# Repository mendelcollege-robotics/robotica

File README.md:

# About
This is the repository for all the files associated with, and used to create, a soccer robot for participation in the [Robocup](https://www.robocup.org/leagues/18). Made by students of the Mendelcollege, from team 'Mendel'.

# Info:

  [Mendelcollege.nl](https://mendelcollege.nl/ontdek-je-talenten/robotica-en-beta/)

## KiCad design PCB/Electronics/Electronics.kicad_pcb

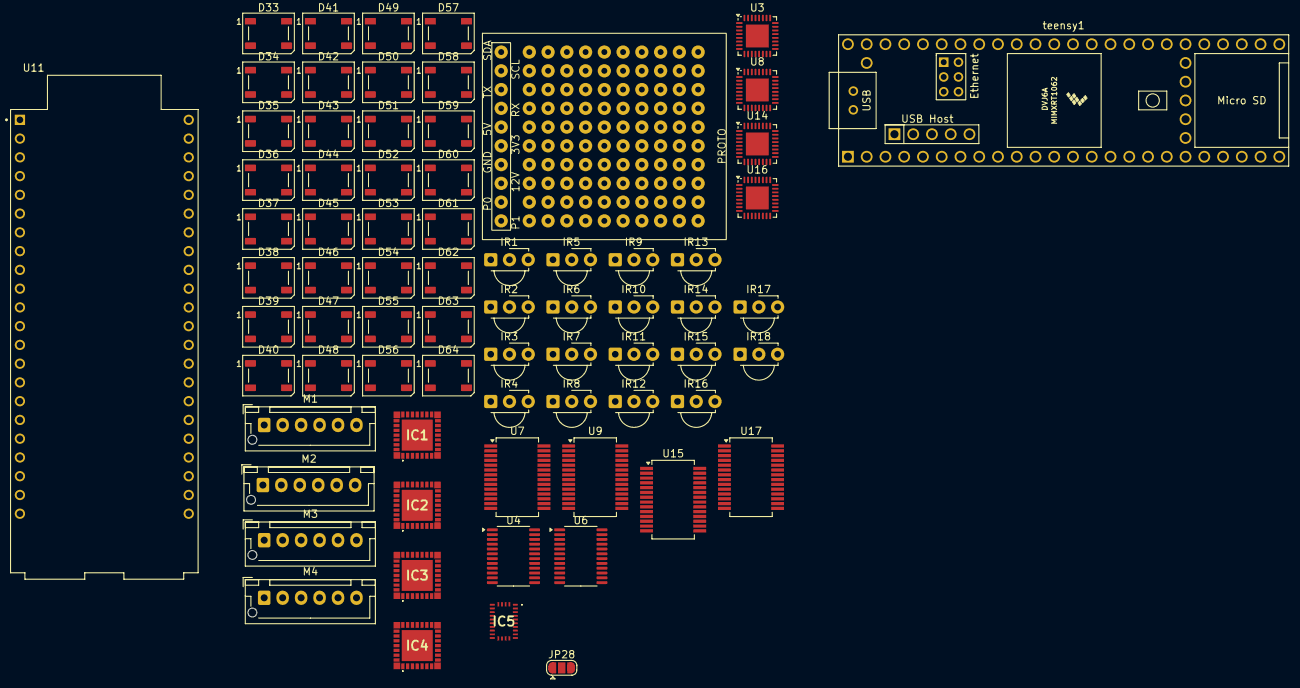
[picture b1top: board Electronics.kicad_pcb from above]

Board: 2 copper layers, 73 parts (0 on the bottom side), 102 nets, no tracks yet.

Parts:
D33, D34, D35, D36, D37, D38, D39, D40, D41, D42, D43, D44, D45, D46, D47, D48, D49, D50, D51, D52, D53, D54, D55, D56, D57, D58, D59, D60, D61, D62, D63, D64: WS2812B; LED_WS2812B_PLCC4_5.0x5.0mm_P3.2mm
IC1, IC2, IC3, IC4: TB9051FTG
IC5: BNO086
IR1, IR2, IR3, IR4, IR5, IR6, IR7, IR8, IR9, IR10, IR11, IR12, IR13, IR14, IR15, IR16, IR17, IR18: TSSP4038; Vishay_MINICAST-3Pin
JP28: SolderJumper_3_Bridged12; SolderJumper-3_P1.3mm_Open_RoundedPad1.0x1.5mm
M1, M2, M3, M4: JST_XH_B6B-XH-AM_1x06_P2.50mm_Vertical
U2: protoboard
U3, U8, U14, U16: ATmega328P-M; QFN-32-1EP_5x5mm_P0.5mm_EP3.1x3.1mm
U4, U6: TCA9548APWR; TSSOP-24_4.4x7.8mm_P0.65mm
U7, U9, U15, U17: FT232RL; SSOP-28_5.3x10.2mm_P0.65mm
U11: ESP32-S3-DEVKITM-1-N8; MODULE_ESP32-S3-DEVKITM-1-N8
teensy1: Teensy4.1; Teensy41

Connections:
+3.3V: U4.24 (VCC), U6.24 (VCC)
+3V3: IC5.3 (VDD), IC5.28 (VDDIO), U2.6 (3.3v), U11.J1_1 (3V3)
+5V: IC1.2 (VCC), IC2.2 (VCC), IC3.2 (VCC), IC4.2 (VCC), M1.3 (5V), M2.3 (5V), M3.3 (5V), M4.3 (5V), U2.5 (5v), U3.4 (VCC), U3.6 (VCC), U3.18 (AVCC), U7.4 (VCCIO), U7.20 (VCC), U8.4 (VCC), U8.6 (VCC), U8.18 (AVCC), U9.4 (VCCIO), U9.20 (VCC), U14.4 (VCC), U14.6 (VCC), U14.18 (AVCC), U15.4 (VCCIO), U15.20 (VCC), U16.4 (VCC), U16.6 (VCC), U16.18 (AVCC), U17.4 (VCCIO), U17.20 (VCC), teensy1.48 (VIN)
/5V: D33.1 (VDD), D34.1 (VDD), D35.1 (VDD), D36.1 (VDD), D37.1 (VDD), D38.1 (VDD), D39.1 (VDD), D40.1 (VDD), D41.1 (VDD), D42.1 (VDD), D43.1 (VDD), D44.1 (VDD), D45.1 (VDD), D46.1 (VDD), D47.1 (VDD), D48.1 (VDD), D49.1 (VDD), D50.1 (VDD), D51.1 (VDD), D52.1 (VDD), D53.1 (VDD), D54.1 (VDD), D55.1 (VDD), D56.1 (VDD), D57.1 (VDD), D58.1 (VDD), D59.1 (VDD), D60.1 (VDD), D61.1 (VDD), D62.1 (VDD), D63.1 (VDD), D64.1 (VDD)
/SCL: IC5.19 (H_SCL/SCK/RX), U2.1 (SCL), U4.22 (SCL), U6.22 (SCL), teensy1.41 (19_A5_SCL)
/SDA: IC5.20 (H_SDA/H_MISO/TX), U4.23 (SDA), U6.23 (SDA), teensy1.40 (18_A4_SDA)
/csn-imu: IC5.18 (H_CSN), teensy1.32 (40_A16)
/encA-m1: M4.5 (encA), U8.24 (PC1)
/encA-m2: M1.5 (encA), U3.24 (PC1)
/encA-m3: M2.5 (encA), U14.24 (PC1)
/encA-m4: M3.5 (encA), U16.24 (PC1)
/encB-m1: M4.6 (encB), U8.25 (PC2)
/encB-m2: M1.6 (encB), U3.25 (PC2)
/encB-m3: M2.6 (encB), U14.25 (PC2)
/encB-m4: M3.6 (encB), U16.25 (PC2)
/esp-rx: U11.J3_6 (U0TXD), teensy1.17 (25_A11_RX6_SDA2)
/esp-tx: U11.J3_5 (U0RXD), teensy1.16 (24_A10_TX6_SCL2)
/int-imu: IC5.14 (H_INTN), teensy1.31 (39_MISO1_OUT1A)
/out1-m1: IC1.13 (OUT1_1), IC1.14 (OUT1_2), M4.1 (+)
/out1-m2: IC2.13 (OUT1_1), IC2.14 (OUT1_2), M1.1 (+)
/out1-m3: IC3.13 (OUT1_1), IC3.14 (OUT1_2), M2.1 (+)
/out1-m4: IC4.13 (OUT1_1), IC4.14 (OUT1_2), M3.1 (+)
/out2-m1: IC1.22 (OUT2_1), IC1.23 (OUT2_2), M4.2 (-)
/out2-m2: IC2.22 (OUT2_1), IC2.23 (OUT2_2), M1.2 (-)
/out2-m3: IC3.22 (OUT2_1), IC3.23 (OUT2_2), M2.2 (-)
/out2-m4: IC4.22 (OUT2_1), IC4.23 (OUT2_2), M3.2 (-)
/pwm1-m1: IC1.8 (PWM1), U8.9 (PD5)
/pwm1-m2: IC2.8 (PWM1), U3.9 (PD5)
/pwm1-m3: IC3.8 (PWM1), U14.9 (PD5)
/pwm1-m4: IC4.8 (PWM1), U16.9 (PD5)
/pwm2-m1: IC1.9 (PWM2), U8.10 (PD6)
/pwm2-m2: IC2.9 (PWM2), U3.10 (PD6)
/pwm2-m3: IC3.9 (PWM2), U14.10 (PD6)
/pwm2-m4: IC4.9 (PWM2), U16.10 (PD6)
/rst-imu: IC5.11 (NRST), teensy1.33 (41_A17)
/rx-m1: U9.1 (TXD), teensy1.2 (0_RX1_CRX2_CS1)
/rx-m2: U7.1 (TXD), teensy1.9 (7_RX2_OUT1A)
/rx-m3: U15.1 (TXD), teensy1.20 (28_RX7)
/rx-m4: U17.1 (TXD), teensy1.26 (34_RX8)
/rx-proto: U2.4 (RX), teensy1.37 (15_A1_RX3_SPDIF_IN)
/tx-m1: U9.5 (RXD), teensy1.3 (1_TX1_CTX2_MISO1)
/tx-m2: U7.5 (RXD), teensy1.10 (8_TX2_IN1)
/tx-m3: U15.5 (RXD), teensy1.21 (29_TX7)
/tx-m4: U17.5 (RXD), teensy1.27 (35_TX8)
/tx-proto: U2.3 (TX), teensy1.36 (14_A0_TX3_SPDIF_OUT)
/vout-m1: IC1.11 (VBAT_1), IC1.12 (VBAT_2), IC1.24 (VBAT_3), IC1.25 (VBAT_4)
/vout-m2: IC2.11 (VBAT_1), IC2.12 (VBAT_2), IC2.24 (VBAT_3), IC2.25 (VBAT_4)
/vout-m3: IC3.11 (VBAT_1), IC3.12 (VBAT_2), IC3.24 (VBAT_3), IC3.25 (VBAT_4)
/vout-m4: IC4.11 (VBAT_1), IC4.12 (VBAT_2), IC4.24 (VBAT_3), IC4.25 (VBAT_4)
GND: D33.3 (VSS), D34.3 (VSS), D35.3 (VSS), D36.3 (VSS), D37.3 (VSS), D38.3 (VSS), D39.3 (VSS), D40.3 (VSS), D41.3 (VSS), D42.3 (VSS), D43.3 (VSS), D44.3 (VSS), D45.3 (VSS), D46.3 (VSS), D47.3 (VSS), D48.3 (VSS), D49.3 (VSS), D50.3 (VSS), D51.3 (VSS), D52.3 (VSS), D53.3 (VSS), D54.3 (VSS), D55.3 (VSS), D56.3 (VSS), D57.3 (VSS), D58.3 (VSS), D60.3 (VSS), D61.3 (VSS), D62.3 (VSS), D63.3 (VSS), D64.3 (VSS), IC1.4 (AGND), IC1.15 (PGND_1), IC1.16 (PGND_2), IC1.17 (PGND_3), IC1.19 (PGND_4), IC1.20 (PGND_5), IC1.21 (PGND_6), IC1.27 (TEST1), IC1.28 (TEST2), IC1.29 (EP), IC1.C1 (CORNER1), IC1.C2 (CORNER2), IC1.C3 (CORNER3), IC1.C4 (CORNER4), IC2.4 (AGND), IC2.15 (PGND_1), IC2.16 (PGND_2), IC2.17 (PGND_3), IC2.19 (PGND_4), IC2.20 (PGND_5), IC2.21 (PGND_6), IC2.27 (TEST1), IC2.28 (TEST2), IC2.29 (EP), IC2.C1 (CORNER1), IC2.C2 (CORNER2), IC2.C3 (CORNER3), IC2.C4 (CORNER4), IC3.4 (AGND), IC3.15 (PGND_1), IC3.16 (PGND_2), IC3.17 (PGND_3), IC3.19 (PGND_4), IC3.20 (PGND_5), IC3.21 (PGND_6), IC3.27 (TEST1), IC3.28 (TEST2), IC3.29 (EP), IC3.C1 (CORNER1), IC3.C2 (CORNER2), IC3.C3 (CORNER3), IC3.C4 (CORNER4), IC4.4 (AGND), IC4.15 (PGND_1), IC4.16 (PGND_2), IC4.17 (PGND_3), IC4.19 (PGND_4), IC4.20 (PGND_5), IC4.21 (PGND_6), IC4.27 (TEST1), IC4.28 (TEST2), IC4.29 (EP), IC4.C1 (CORNER1), IC4.C2 (CORNER2), IC4.C3 (CORNER3), IC4.C4 (CORNER4), IC5.2 (GND_1), IC5.10 (CLKSEL0), IC5.25 (GND_2), IR1.2 (GND), IR2.2 (GND), IR3.2 (GND), IR4.2 (GND), IR5.2 (GND), IR6.2 (GND), IR7.2 (GND), IR8.2 (GND), IR9.2 (GND), IR10.2 (GND), IR11.2 (GND), IR12.2 (GND), IR13.2 (GND), IR14.2 (GND), IR15.2 (GND), IR16.2 (GND), IR17.2 (GND), IR18.2 (GND), M1.4 (GND), M2.4 (GND), M3.4 (GND), M4.4 (GND), U2.7 (gnd), U3.3 (GND), U3.5 (GND), U3.21 (GND), U3.33 (GND), U4.12 (GND), U6.12 (GND), U7.7 (GND), U7.18 (GND), U7.21 (GND), U7.25 (AGND), U7.26 (TEST), U8.3 (GND), U8.5 (GND), U8.21 (GND), U8.33 (GND), U9.7 (GND), U9.18 (GND), U9.21 (GND), U9.25 (AGND), U9.26 (TEST), U11.J3_1 (GND_J3_1), U14.3 (GND), U14.5 (GND), U14.21 (GND), U14.33 (GND), U15.7 (GND), U15.18 (GND), U15.21 (GND), U15.25 (AGND), U15.26 (TEST), U16.3 (GND), U16.5 (GND), U16.21 (GND), U16.33 (GND), U17.7 (GND), U17.18 (GND), U17.21 (GND), U17.25 (AGND), U17.26 (TEST), teensy1.1 (GND), teensy1.34 (GND), teensy1.47 (GND)
unnamed: D33.2 (DOUT), D37.4 (DIN)
unnamed: D34.4 (DIN), D61.2 (DOUT)
unnamed: D34.2 (DOUT), D38.4 (DIN)
unnamed: D35.4 (DIN), D62.2 (DOUT)
unnamed: D35.2 (DOUT), D39.4 (DIN)
unnamed: D36.4 (DIN), D63.2 (DOUT)
unnamed: D36.2 (DOUT), D40.4 (DIN)
unnamed: D37.2 (DOUT), D41.4 (DIN)
unnamed: D38.2 (DOUT), D42.4 (DIN)
unnamed: D39.2 (DOUT), D43.4 (DIN)
unnamed: D40.2 (DOUT), D44.4 (DIN)
unnamed: D41.2 (DOUT), D45.4 (DIN)
unnamed: D42.2 (DOUT), D46.4 (DIN)
unnamed: D43.2 (DOUT), D47.4 (DIN)
unnamed: D44.2 (DOUT), D48.4 (DIN)
unnamed: D45.2 (DOUT), D49.4 (DIN)
unnamed: D46.2 (DOUT), D50.4 (DIN)
unnamed: D47.2 (DOUT), D51.4 (DIN)
unnamed: D48.2 (DOUT), D52.4 (DIN)
unnamed: D49.2 (DOUT), D53.4 (DIN)
unnamed: D50.2 (DOUT), D54.4 (DIN)
unnamed: D51.2 (DOUT), D55.4 (DIN)
unnamed: D52.2 (DOUT), D56.4 (DIN)
unnamed: D53.2 (DOUT), D57.4 (DIN)
unnamed: D54.2 (DOUT), D58.4 (DIN)
unnamed: D55.2 (DOUT), D59.4 (DIN)
unnamed: D56.2 (DOUT), D60.4 (DIN)
unnamed: D57.2 (DOUT), D61.4 (DIN)
unnamed: D58.2 (DOUT), D62.4 (DIN)
unnamed: D59.2 (DOUT), D63.4 (DIN)
unnamed: D60.2 (DOUT), D64.4 (DIN)
unnamed: IC5.5 (PS1), JP28.2 (C)
unnamed: IR1.1 (OUT), U11.J1_2 (GPIO0)
unnamed: IR2.1 (OUT), U11.J1_3 (GPIO1)
unnamed: IR3.1 (OUT), U11.J1_4 (GPIO2)
unnamed: IR4.1 (OUT), U11.J1_5 (GPIO3)
unnamed: IR5.1 (OUT), U11.J1_6 (GPIO4)
unnamed: IR6.1 (OUT), U11.J1_7 (GPIO5)
unnamed: IR7.1 (OUT), U11.J1_8 (GPIO6)
unnamed: IR8.1 (OUT), U11.J1_9 (GPIO7)
unnamed: IR9.1 (OUT), U11.J1_10 (GPIO8)
unnamed: IR10.1 (OUT), U11.J1_11 (GPIO9)
unnamed: IR11.1 (OUT), U11.J1_12 (GPIO10)
unnamed: IR12.1 (OUT), U11.J1_13 (GPIO11)
unnamed: IR13.1 (OUT), U11.J1_14 (GPIO12)
unnamed: IR14.1 (OUT), U11.J1_15 (GPIO13)
unnamed: IR15.1 (OUT), U11.J1_16 (GPIO14)
unnamed: IR16.1 (OUT), U11.J1_17 (GPIO15)
unnamed: IR17.1 (OUT), U11.J1_18 (GPIO16)
unnamed: IR18.1 (OUT), U11.J1_19 (GPIO17)
unnamed: U2.9 (P0), teensy1.19 (27_A13_SCK1)
unnamed: U2.10 (P1), teensy1.18 (26_A12_MOSI1)

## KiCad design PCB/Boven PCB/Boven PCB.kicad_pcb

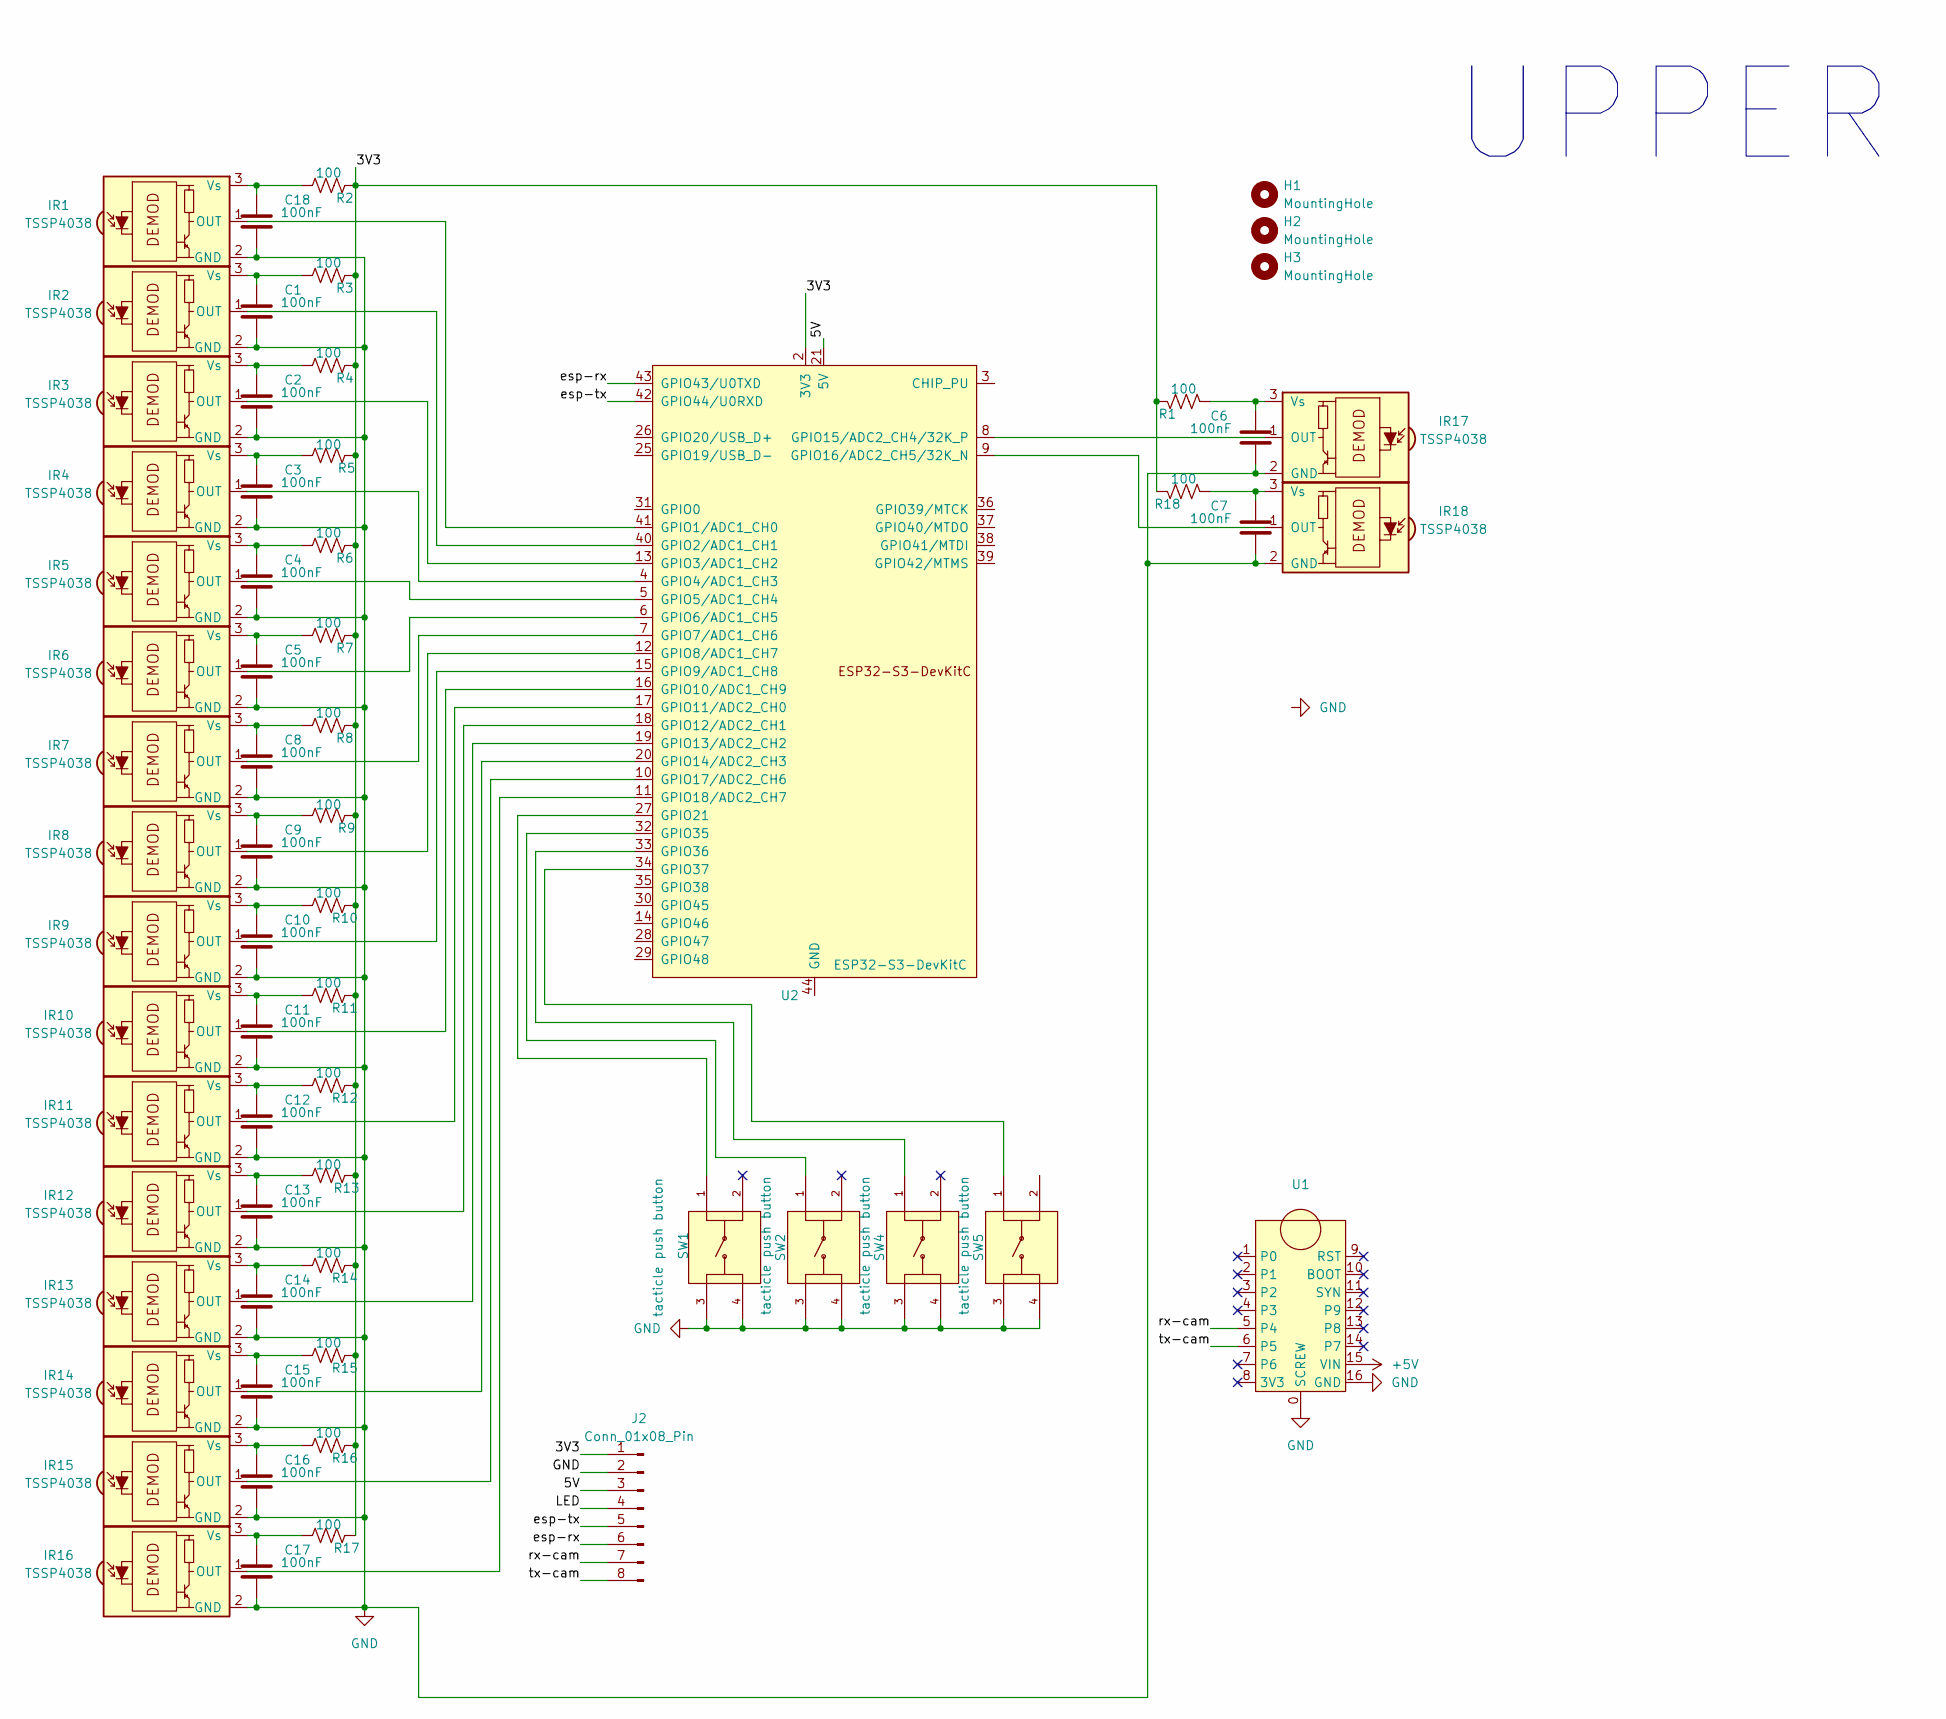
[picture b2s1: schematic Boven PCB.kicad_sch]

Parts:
C1, C2, C3, C4, C5, C6, C7, C8, C9, C10, C11, C12, C13, C14, C15, C16, C17, C18: 100nF; C_0603_1608Metric_Pad1.08x0.95mm_HandSolder
H1, H2, H3: MountingHole; MountingHole_4mm
IR1, IR2, IR3, IR4, IR5, IR6, IR7, IR8, IR9, IR10, IR11, IR12, IR13, IR14, IR15, IR16, IR17, IR18: TSSP4038; Vishay_MINICAST-3Pin
J2: Conn_01x08_Pin; JST_EH_B8B-EH-A_1x08_P2.50mm_Vertical
R1, R2, R3, R4, R5, R6, R7, R8, R9, R10, R11, R12, R13, R14, R15, R16, R17, R18: 100; R_0603_1608Metric_Pad0.98x0.95mm_HandSolder
SW1, SW2, SW4, SW5: tacticle push button; SW_Push_2P1T_Toggle_CK_PVA1xxH4xxxxxxV2; PARTREV C10
U1: openMV_H7
U2: ESP32-S3-DevKitC

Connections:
/3V3: J2.1, R1.2, R2.2, R3.2, R4.2, R5.2, R6.2, R7.2, R8.2, R9.2, R10.2, R11.2, R12.2, R13.2, R14.2, R15.2, R16.2, R17.2, R18.2, U2.1 (3V3), U2.2 (3V3); also elsewhere on the board
/LED: J2.4
/esp-rx: J2.6, U2.43 (GPIO43/U0TXD); also elsewhere on the board
/esp-tx: J2.5, U2.42 (GPIO44/U0RXD); also elsewhere on the board
/rx-cam: J2.7, U1.5 (P4)
/tx-cam: J2.8, U1.6 (P5)
GND: C1.2, C2.2, C3.2, C4.2, C5.2, C6.2, C7.2, C8.2, C9.2, C10.2, C11.2, C12.2, C13.2, C14.2, C15.2, C16.2, C17.2, C18.2, IR1.2 (GND), IR2.2 (GND), IR3.2 (GND), IR4.2 (GND), IR5.2 (GND), IR6.2 (GND), IR7.2 (GND), IR8.2 (GND), IR9.2 (GND), IR10.2 (GND), IR11.2 (GND), IR12.2 (GND), IR13.2 (GND), IR14.2 (GND), IR15.2 (GND), IR16.2 (GND), IR17.2 (GND), IR18.2 (GND), J2.2, SW1.3, SW1.4, SW2.3, SW2.4, SW4.3, SW4.4, SW5.3, SW5.4, U1.0 (SCREW), U1.16 (GND); also elsewhere on the board
unnamed 7: IR1.1 (OUT), U2.41 (GPIO1/ADC1_CH0); also elsewhere on the board
unnamed: C18.1, IR1.3 (Vs), R2.1
unnamed 9: IR2.1 (OUT), U2.40 (GPIO2/ADC1_CH1); also elsewhere on the board
unnamed: C1.1, IR2.3 (Vs), R3.1
unnamed 11: IR3.1 (OUT), U2.13 (GPIO3/ADC1_CH2); also elsewhere on the board
unnamed: C2.1, IR3.3 (Vs), R4.1
unnamed 13: IR4.1 (OUT), U2.4 (GPIO4/ADC1_CH3); also elsewhere on the board
unnamed: C3.1, IR4.3 (Vs), R5.1
unnamed 15: IR5.1 (OUT), U2.5 (GPIO5/ADC1_CH4); also elsewhere on the board
unnamed: C4.1, IR5.3 (Vs), R6.1
unnamed 17: IR6.1 (OUT), U2.6 (GPIO6/ADC1_CH5); also elsewhere on the board
unnamed: C5.1, IR6.3 (Vs), R7.1
unnamed 19: IR7.1 (OUT), U2.7 (GPIO7/ADC1_CH6); also elsewhere on the board
unnamed: C8.1, IR7.3 (Vs), R8.1
unnamed 21: IR8.1 (OUT), U2.12 (GPIO8/ADC1_CH7); also elsewhere on the board
unnamed: C9.1, IR8.3 (Vs), R9.1
unnamed 23: IR9.1 (OUT), U2.15 (GPIO9/ADC1_CH8); also elsewhere on the board
unnamed: C10.1, IR9.3 (Vs), R10.1
unnamed 25: IR10.1 (OUT), U2.16 (GPIO10/ADC1_CH9); also elsewhere on the board
unnamed: C11.1, IR10.3 (Vs), R11.1
unnamed 27: IR11.1 (OUT), U2.17 (GPIO11/ADC2_CH0); also elsewhere on the board
unnamed: C12.1, IR11.3 (Vs), R12.1
unnamed 29: IR12.1 (OUT), U2.18 (GPIO12/ADC2_CH1); also elsewhere on the board
unnamed: C13.1, IR12.3 (Vs), R13.1
unnamed 31: IR13.1 (OUT), U2.19 (GPIO13/ADC2_CH2); also elsewhere on the board
unnamed: C14.1, IR13.3 (Vs), R14.1
unnamed 33: IR14.1 (OUT), U2.20 (GPIO14/ADC2_CH3); also elsewhere on the board
unnamed: C15.1, IR14.3 (Vs), R15.1
unnamed 35: IR15.1 (OUT), U2.10 (GPIO17/ADC2_CH6); also elsewhere on the board
unnamed: C16.1, IR15.3 (Vs), R16.1
unnamed 37: IR16.1 (OUT), U2.11 (GPIO18/ADC2_CH7); also elsewhere on the board
unnamed: C17.1, IR16.3 (Vs), R17.1
unnamed 39: IR17.1 (OUT), U2.8 (GPIO15/ADC2_CH4/32K_P); also elsewhere on the board
unnamed: C6.1, IR17.3 (Vs), R1.1
unnamed 41: IR18.1 (OUT), U2.9 (GPIO16/ADC2_CH5/32K_N); also elsewhere on the board
unnamed: C7.1, IR18.3 (Vs), R18.1
unnamed 43: SW1.1, U2.27 (GPIO21); also elsewhere on the board
unnamed 44: SW2.1, U2.32 (GPIO35); also elsewhere on the board
unnamed 45: SW4.1, U2.33 (GPIO36); also elsewhere on the board
unnamed 46: SW5.1, U2.34 (GPIO37); also elsewhere on the board
unnamed: U2.22 (GND), U2.23 (GND), U2.24 (GND), U2.44 (GND)

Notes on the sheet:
UPPER

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
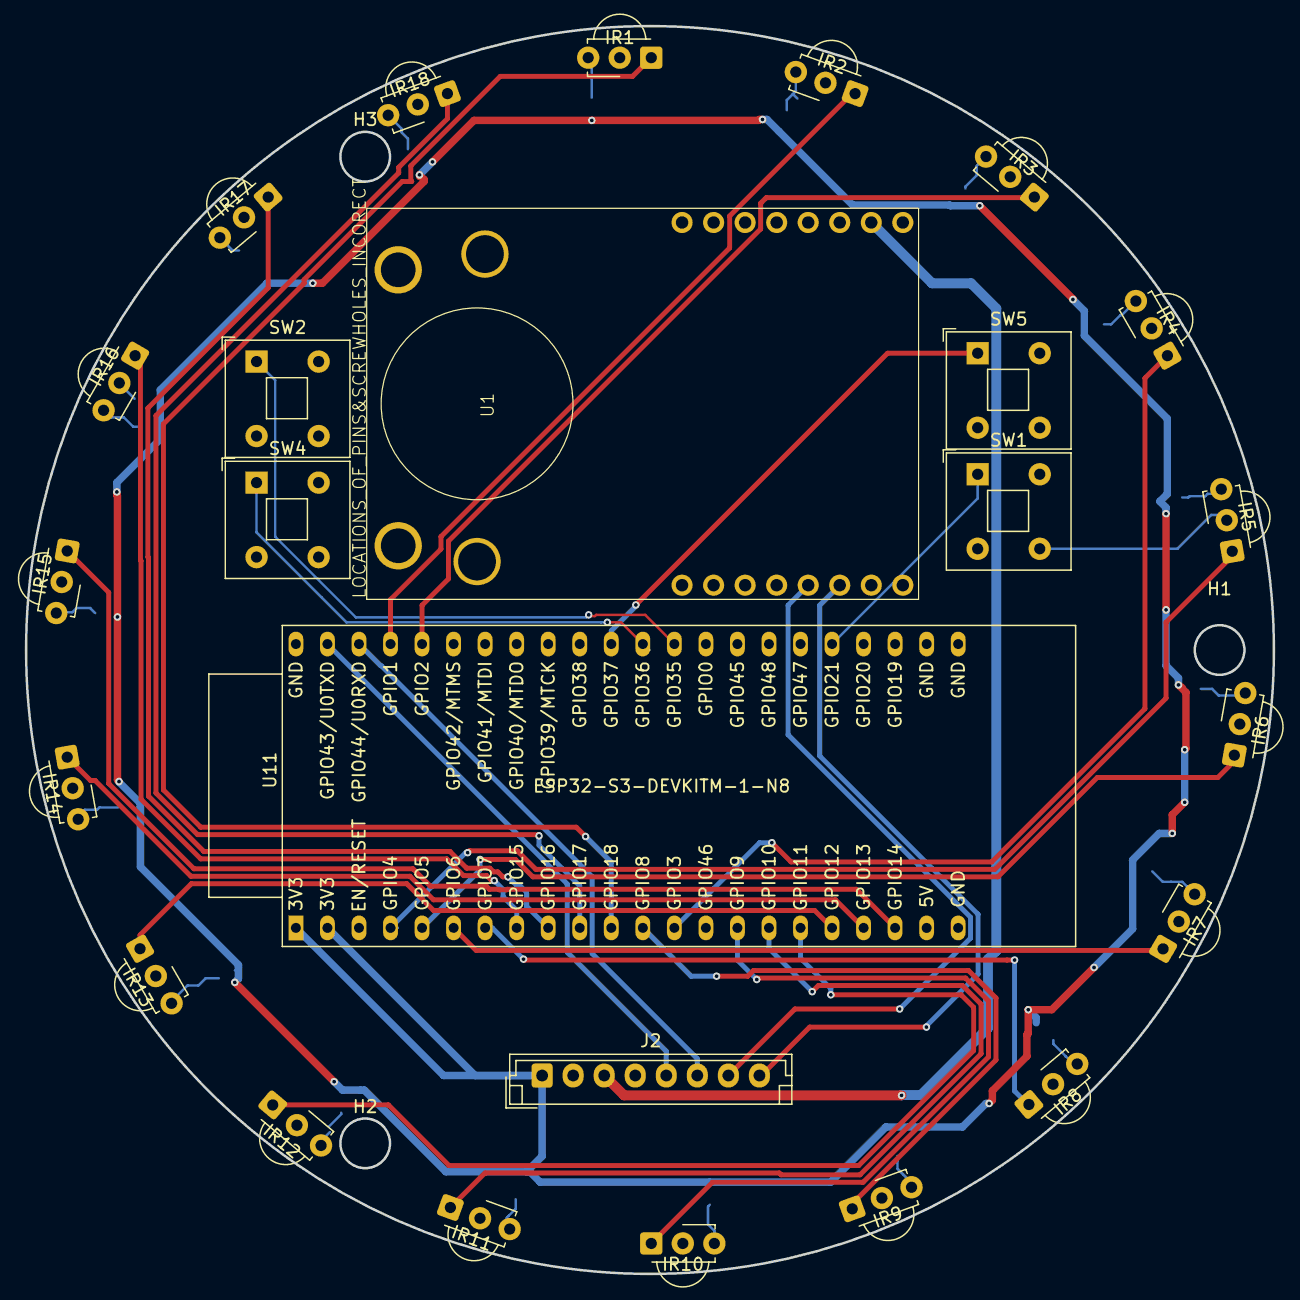
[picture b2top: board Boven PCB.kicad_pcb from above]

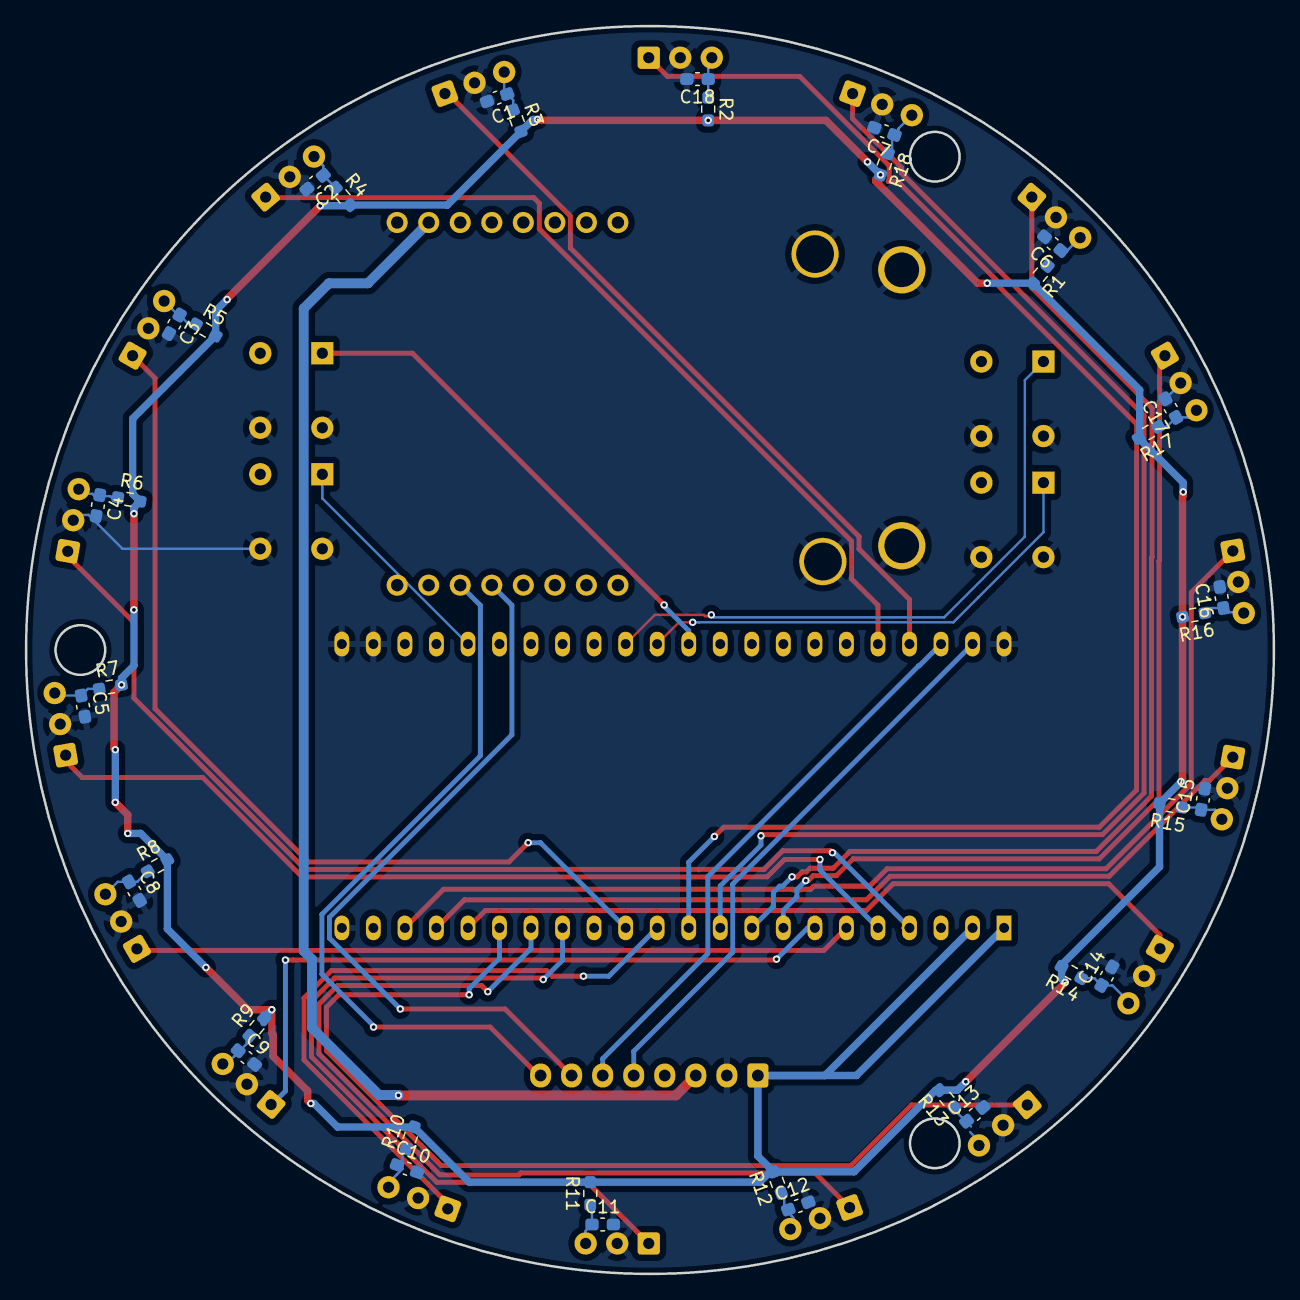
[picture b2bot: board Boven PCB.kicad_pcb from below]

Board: 2 copper layers, 100.5 x 100.5 mm, 64 parts (36 on the bottom side), 47 nets.

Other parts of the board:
U11: ESP32-S3-DEVKITM-1-N8; test

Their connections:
/3V3: U11.J1_0 (3V3), U11.J1_1 (3V3); also elsewhere on the board
/esp-rx: U11.J3_5; also elsewhere on the board
/esp-tx: U11.J3_6; also elsewhere on the board
GND: U11.24, U11.J1_22, U11.J3_1; also elsewhere on the board
unnamed 7: U11.J2_9; also elsewhere on the board
unnamed 9: U11.J1_3 (GPIO1); also elsewhere on the board
unnamed 11: U11.J1_4 (GPIO2); also elsewhere on the board
unnamed 13: U11.J1_5 (GPIO3); also elsewhere on the board
unnamed 15: U11.J1_6 (GPIO4); also elsewhere on the board
unnamed 17: U11.J1_7 (GPIO5); also elsewhere on the board
unnamed 19: U11.J1_8 (GPIO6); also elsewhere on the board
unnamed 21: U11.J1_9 (GPIO7); also elsewhere on the board
unnamed 23: U11.J1_10 (GPIO8); also elsewhere on the board
unnamed 25: U11.J2_0; also elsewhere on the board
unnamed 27: U11.J2_1; also elsewhere on the board
unnamed 29: U11.J2_2; also elsewhere on the board
unnamed 31: U11.J2_3; also elsewhere on the board
unnamed 33: U11.J2_4; also elsewhere on the board
unnamed 35: U11.J2_5; also elsewhere on the board
unnamed 37: U11.J2_6 (GPIO6); also elsewhere on the board
unnamed 39: U11.J2_7 (GPIO7); also elsewhere on the board
unnamed 41: U11.J2_8 (GPIO8); also elsewhere on the board
unnamed 43: U11.J3_18; also elsewhere on the board
unnamed 44: U11.J3_14; also elsewhere on the board
unnamed 45: U11.J3_13; also elsewhere on the board
unnamed 46: U11.J3_12; also elsewhere on the board

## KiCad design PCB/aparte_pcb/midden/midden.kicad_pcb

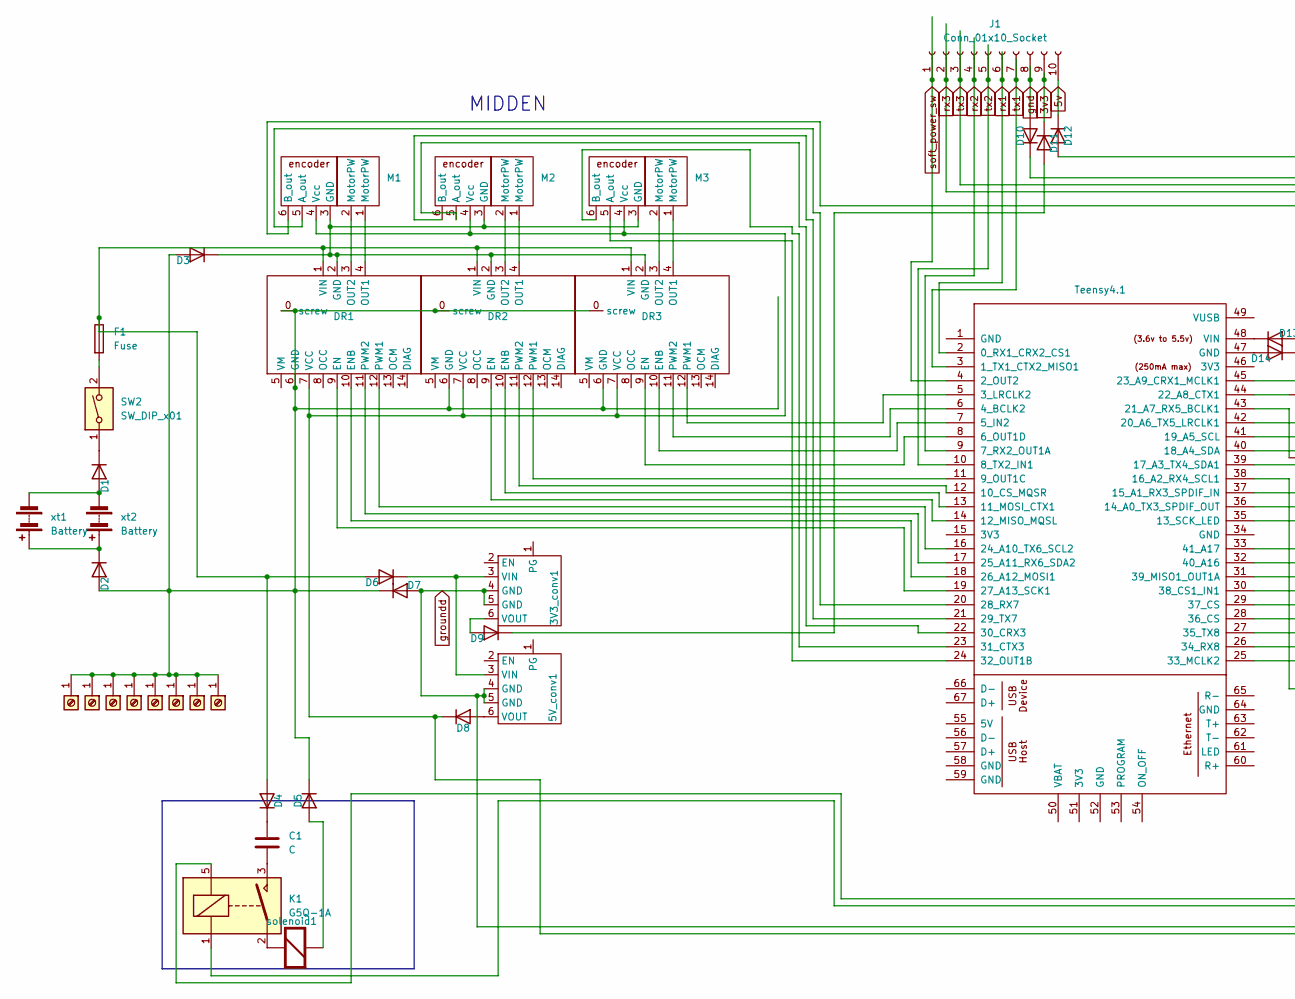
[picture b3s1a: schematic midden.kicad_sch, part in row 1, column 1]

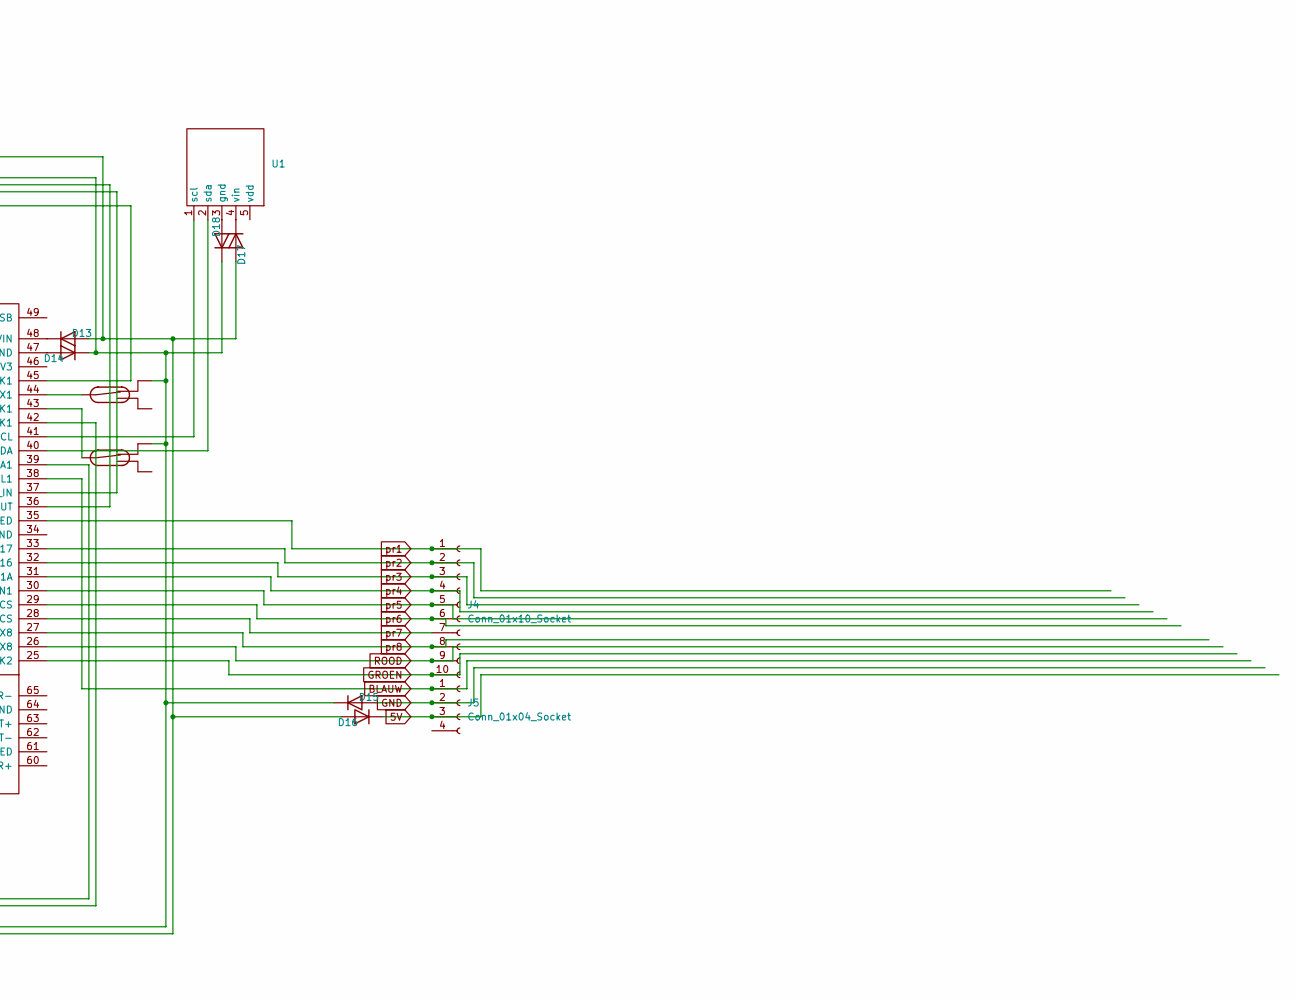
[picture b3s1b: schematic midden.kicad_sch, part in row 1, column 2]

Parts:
3V3_conv1, 5V_conv1: pololu-d30v30fx
C1: C; CP_Radial_D8.0mm_P3.50mm
D1, D2, D3, D4, D5, D6, D7, D8, D9, D10, D11, D12, D13, D14, D15, D16, D17, D18: D; D_MELF-RM10_Universal_Handsoldering
DR1, DR2, DR3: TB9051FTG
F1: Fuse; Fuseholder_TR5_Littelfuse_No560_No460
J1, J4: Conn_01x10_Socket; JST_EH_S10B-EH_1x10_P2.50mm_Horizontal
J2, J3, J6, J7, J8, J9, J10, J11: Screw_Terminal_01x01; MountingHole_4.3mm_M4_ISO7380_Pad
J5: Conn_01x04_Socket; JST_EH_S4B-EH_1x04_P2.50mm_Horizontal
K1: G5Q-1A; Relay_SPST_Omron-G5Q-1A
M1, M2, M3: PinHeader_1x06_P1.27mm_Vertical
SW1, SW5: SW_Reed_SPDT; Mini Snap-Action Switch with 13.5mm Lever 3-Pin, SPDT, 1A
SW2: SW_DIP_x01; Rocker Switch 3-Pin, SPDT, 10A
U1: miniIMU
solenoid1: Re; Altech_AK100_1x02_P5.00mm; Rating V/Ω
teensy1: Teensy4.1; Teensy41
xt1: Battery; AMASS_XT60-F_1x02_P7.20mm_Vertical
xt2: Battery; AMASS_XT30U-M_1x02_P5.0mm_Vertical

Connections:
3v3: D11.1 (K), J1.9
5V: D16.1 (K), J5.3
5v: D12.1 (K), J1.10
BLAUW: J5.1, teensy1.38 (16_A2_RX4_SCL1)
GND: D15.2 (A), J5.2
GROEN: J4.10, teensy1.25 (33_MCLK2)
unnamed: 3V3_conv1.3 (VIN), 5V_conv1.3 (VIN), D6.1 (K)
unnamed: 3V3_conv1.6 (VOUT), D9.2 (A)
unnamed: 5V_conv1.6 (VOUT), D8.2 (A)
unnamed: C1.2, K1.3
unnamed: D1.2 (A), xt1.2 (-), xt2.2 (-)
unnamed: D1.1 (K), SW2.1
unnamed: D2.2 (A), D3.2 (A), D5.1 (K), D7.1 (K), DR1.0 (screw), DR1.6 (GND), DR2.0 (screw), DR2.6 (GND), DR3.0 (screw), DR3.6 (GND), J2.1, J3.1, J6.1, J7.1, J8.1, J9.1, J10.1, J11.1
unnamed: D2.1 (K), xt1.1 (+), xt2.1 (+)
unnamed: D3.1 (K), DR1.2 (GND), DR2.2 (GND), DR3.2 (GND), M1.3 (GND), M2.3 (GND), M3.3 (GND)
unnamed: D4.2 (A), D6.2 (A), DR1.1 (VIN), DR2.1 (VIN), DR3.1 (VIN), F1.1
unnamed: C1.1, D4.1 (K)
unnamed: D5.2 (A), solenoid1.2 (-)
unnamed: D9.1 (K), D11.2 (A)
unnamed: D8.1 (K), D12.2 (A), D13.2 (A), D16.2 (A), D17.2 (A), DR1.7 (VCC), DR2.7 (VCC), DR3.7 (VCC), M1.4 (Vcc), M2.4 (Vcc), M3.4 (Vcc)
unnamed: D13.1 (K), teensy1.48 (VIN)
unnamed: D14.2 (A), teensy1.47 (GND)
unnamed: D17.1 (K), U1.4 (vin)
unnamed: D18.2 (A), U1.3 (gnd)
unnamed: DR1.9 (EN), teensy1.19 (27_A13_SCK1)
unnamed: DR1.10 (ENB), teensy1.18 (26_A12_MOSI1)
unnamed: DR1.4 (OUT1), M1.1 (MotorPW)
unnamed: DR1.3 (OUT2), M1.2 (MotorPW)
unnamed: DR1.12 (PWM1), teensy1.16 (24_A10_TX6_SCL2)
unnamed: DR1.11 (PWM2), teensy1.17 (25_A11_RX6_SDA2)
unnamed: DR2.9 (EN), teensy1.14 (12_MISO_MQSL)
unnamed: DR2.10 (ENB), teensy1.13 (11_MOSI_CTX1)
unnamed: DR2.4 (OUT1), M2.1 (MotorPW)
unnamed: DR2.3 (OUT2), M2.2 (MotorPW)
unnamed: DR2.12 (PWM1), teensy1.11 (9_OUT1C)
unnamed: DR2.11 (PWM2), teensy1.12 (10_CS_MQSR)
unnamed: DR3.9 (EN), teensy1.8 (6_OUT1D)
unnamed: DR3.10 (ENB), teensy1.7 (5_IN2)
unnamed: DR3.4 (OUT1), M3.1 (MotorPW)
unnamed: DR3.3 (OUT2), M3.2 (MotorPW)
unnamed: DR3.12 (PWM1), teensy1.5 (3_LRCLK2)
unnamed: DR3.11 (PWM2), teensy1.6 (4_BCLK2)
unnamed: F1.2, SW2.2
unnamed: M1.5 (A_out), teensy1.20 (28_RX7)
unnamed: M1.6 (B_out), teensy1.45 (23_A9_CRX1_MCLK1)
unnamed: M2.5 (A_out), teensy1.22 (30_CRX3)
unnamed: M2.6 (B_out), teensy1.21 (29_TX7)
unnamed: M3.5 (A_out), teensy1.24 (32_OUT1B)
unnamed: M3.6 (B_out), teensy1.23 (31_CTX3)
unnamed: U1.1 (scl), teensy1.41 (19_A5_SCL)
unnamed: U1.2 (sda), teensy1.40 (18_A4_SDA)
unnamed: K1.2, solenoid1.1 (+)
unnamed: K1.5, teensy1.39 (17_A3_TX4_SDA1)
unnamed: K1.1, teensy1.42 (20_A6_TX5_LRCLK1)
unnamed: SW5.2, teensy1.43 (21_A7_RX5_BCLK1)
unnamed: SW1.2, teensy1.44 (22_A8_CTX1)
ROOD: J4.9, teensy1.26 (34_RX8)
gnd: D10.2 (A), J1.8
groundd: 3V3_conv1.4 (GND), 3V3_conv1.5 (GND), 5V_conv1.4 (GND), 5V_conv1.5 (GND), D7.2 (A), D10.1 (K), D14.1 (K), D15.1 (K), D18.1 (K), SW1.1, SW5.1
pr1: J4.1, teensy1.35 (13_SCK_LED)
pr2: J4.2, teensy1.33 (41_A17)
pr3: J4.3, teensy1.32 (40_A16)
pr4: J4.4, teensy1.31 (39_MISO1_OUT1A)
pr5: J4.5, teensy1.30 (38_CS1_IN1)
pr6: J4.6, teensy1.29 (37_CS)
pr7: J4.7, teensy1.28 (36_CS)
pr8: J4.8, teensy1.27 (35_TX8)
rx1: J1.6, teensy1.2 (0_RX1_CRX2_CS1)
rx2: J1.4, teensy1.9 (7_RX2_OUT1A)
rx3: J1.2, teensy1.37 (15_A1_RX3_SPDIF_IN)
soft_power_sw: J1.1, teensy1.4 (2_OUT2)
tx1: J1.7, teensy1.3 (1_TX1_CTX2_MISO1)
tx2: J1.5, teensy1.10 (8_TX2_IN1)
tx3: J1.3, teensy1.36 (14_A0_TX3_SPDIF_OUT)

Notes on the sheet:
MIDDEN

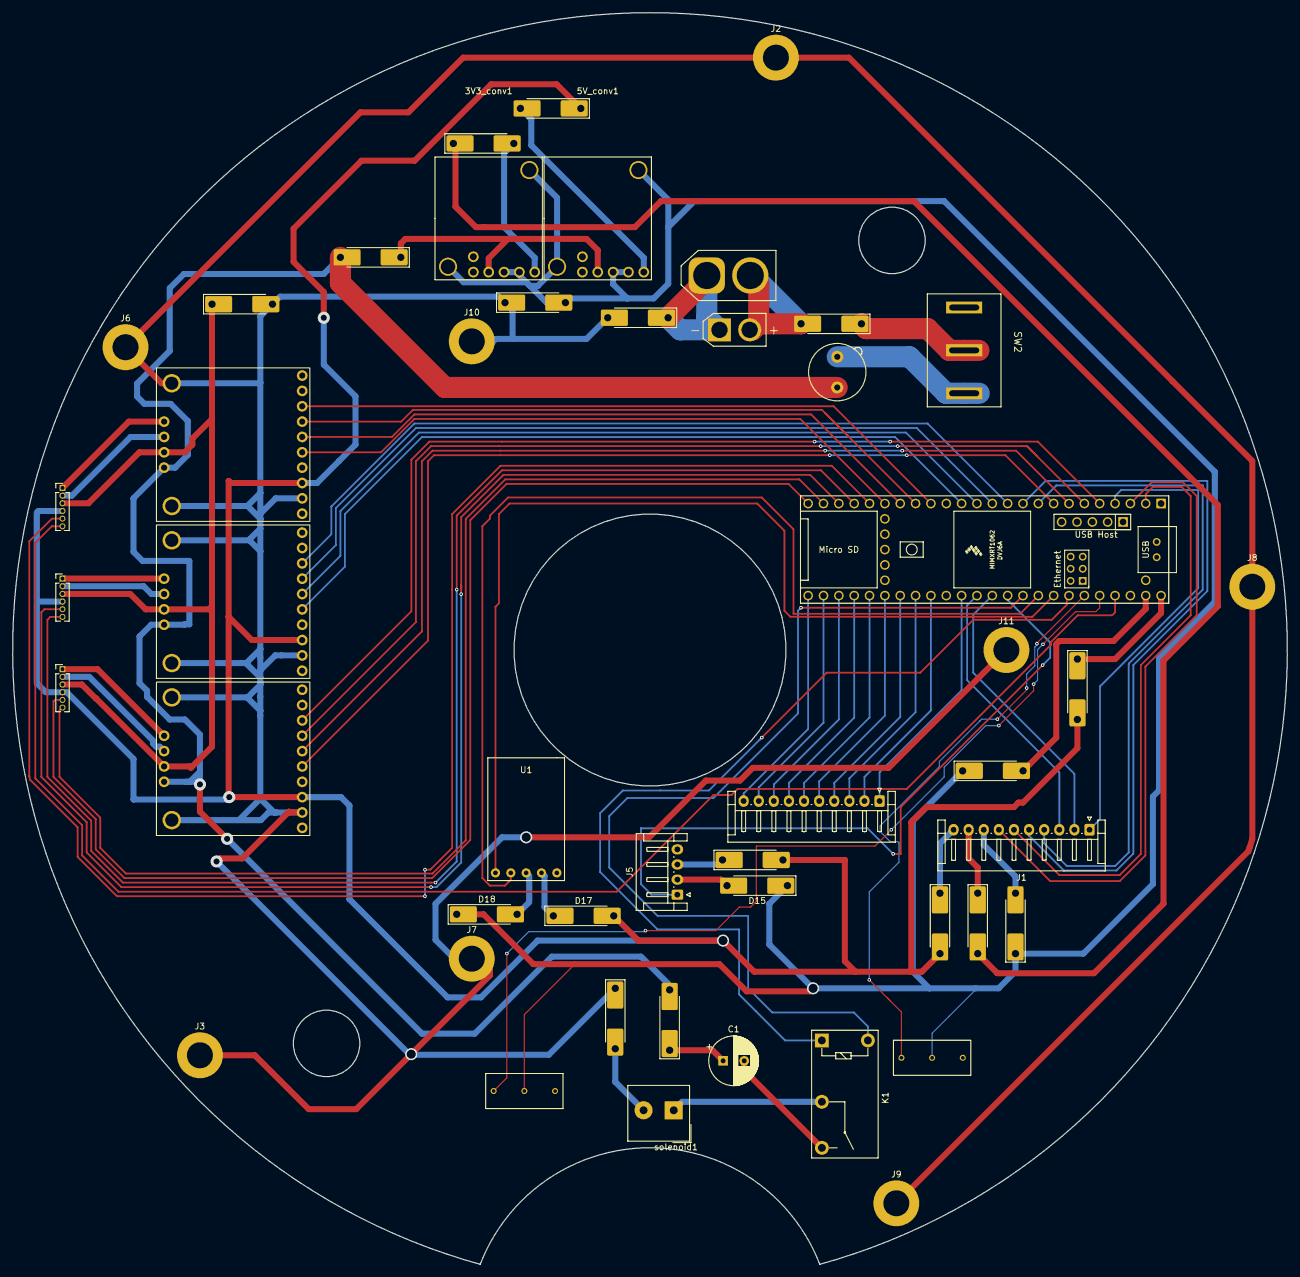
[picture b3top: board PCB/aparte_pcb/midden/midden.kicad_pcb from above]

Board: 2 copper layers, 211.0 x 207.2 mm, 48 parts (0 on the bottom side), 74 nets.
